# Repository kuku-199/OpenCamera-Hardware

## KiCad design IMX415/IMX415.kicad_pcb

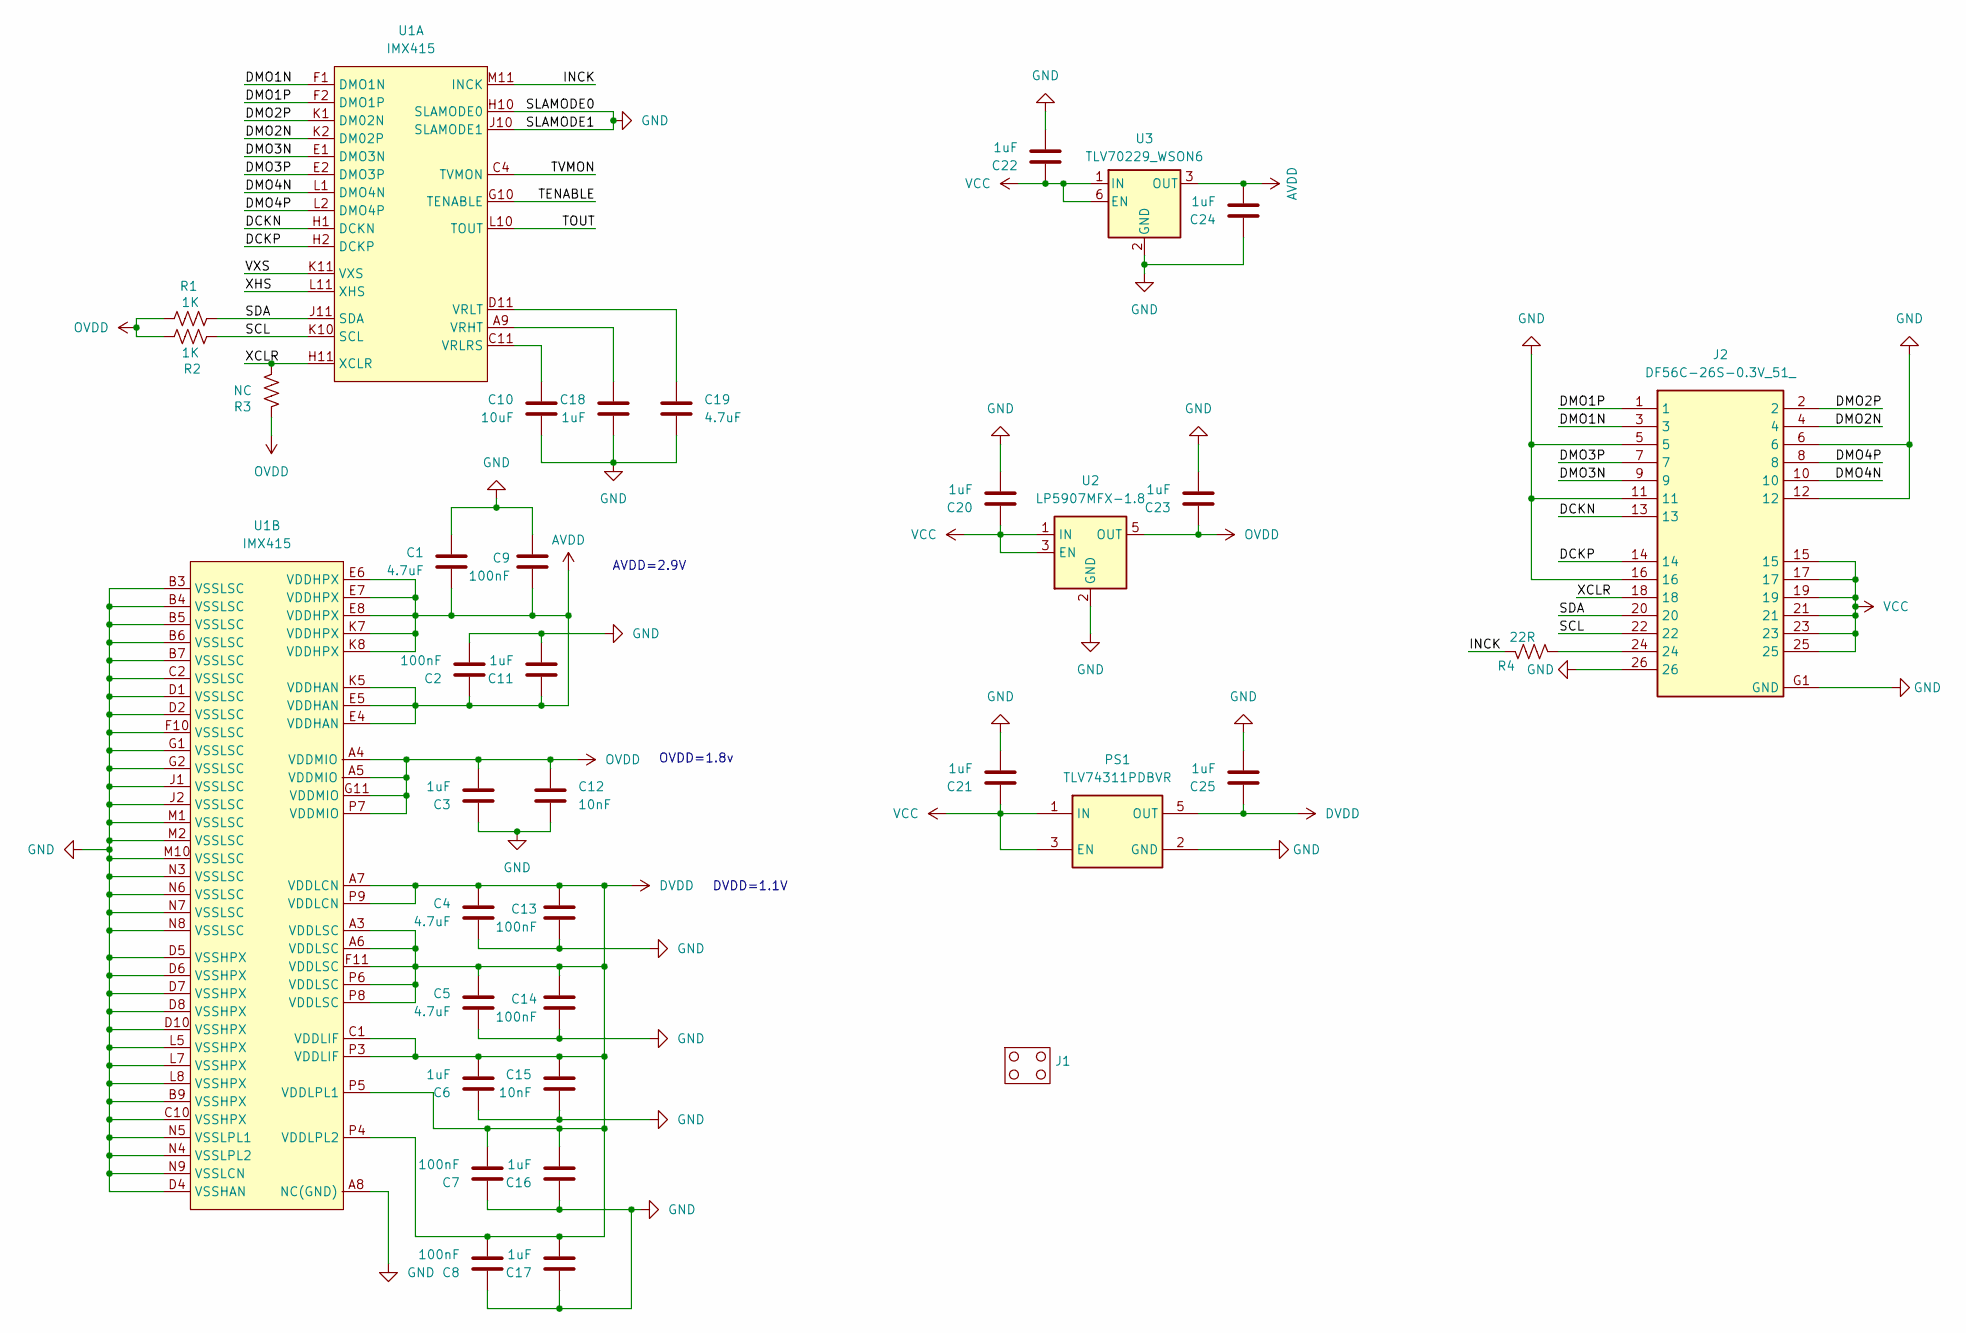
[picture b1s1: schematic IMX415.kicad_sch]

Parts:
C1, C4, C5, C19: 4.7uF; C_0402_1005Metric
C2, C7, C8, C9, C13, C14: 100nF; C_0402_1005Metric
C3, C6, C11, C16, C17, C18, C20, C21, C22, C23, C24, C25: 1uF; C_0402_1005Metric
C10: 10uF; C_0402_1005Metric
C12, C15: 10nF; C_0402_1005Metric
J1: Outline_19X19
J2: DF56C-26S-0.3V_51_; DF56C26S03V51; Manufacturer_Part_Number DF56C-26S-0.3V(51); Mouser Part Number 798-DF56C-26S-0.3V51
PS1: TLV74311PDBVR; SOT95P280X145-5N; Manufacturer_Part_Number TLV74311PDBVR; Mouser Part Number 595-TLV74311PDBVR
R1, R2: 1K; R_0402_1005Metric
R3: NC; R_0402_1005Metric
R4: 22R; R_0402_1005Metric
U1: IMX415
U2: LP5907MFX-1.8; SOT-23-5
U3: TLV70229_WSON6; WSON-6_1.5x1.5mm_P0.5mm

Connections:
/DCKN: J2.13, U1.H1 (DCKN)
/DCKP: J2.14, U1.H2 (DCKP)
/DMO1N: J2.3, U1.F1 (DMO1N)
/DMO1P: J2.1, U1.F2 (DMO1P)
/DMO2N: J2.4, U1.K2 (DM02P)
/DMO2P: J2.2, U1.K1 (DM02N)
/DMO3N: J2.9, U1.E1 (DMO3N)
/DMO3P: J2.7, U1.E2 (DMO3P)
/DMO4N: J2.10, U1.L1 (DMO4N)
/DMO4P: J2.8, U1.L2 (DMO4P)
/INCK: R4.2, U1.M11 (INCK)
/SCL: J2.22, R2.2, U1.K10 (SCL)
/SDA: J2.20, R1.1, U1.J11 (SDA)
/TENABLE: U1.G10 (TENABLE)
/TOUT: U1.L10 (TOUT)
/TVMON: U1.C4 (TVMON)
/VXS: U1.K11 (VXS)
/XCLR: J2.18, R3.1, U1.H11 (XCLR)
/XHS: U1.L11 (XHS)
AVDD: C1.2, C2.1, C9.2, C11.1, C24.2, U1.E4 (VDDHAN), U1.E5 (VDDHAN), U1.E6 (VDDHPX), U1.E7 (VDDHPX), U1.E8 (VDDHPX), U1.K5 (VDDHAN), U1.K7 (VDDHPX), U1.K8 (VDDHPX), U3.3 (OUT)
DVDD: C4.1, C5.1, C6.2, C7.2, C8.2, C13.1, C14.1, C15.2, C16.2, C17.2, C25.1, PS1.5 (OUT), U1.A3 (VDDLSC), U1.A6 (VDDLSC), U1.A7 (VDDLCN), U1.C1 (VDDLIF), U1.F11 (VDDLSC), U1.P3 (VDDLIF), U1.P4 (VDDLPL2), U1.P5 (VDDLPL1), U1.P6 (VDDLSC), U1.P8 (VDDLSC), U1.P9 (VDDLCN)
GND: C1.1, C2.2, C3.1, C4.2, C5.2, C6.1, C7.1, C8.1, C9.1, C10.1, C11.2, C12.1, C13.2, C14.2, C15.1, C16.1, C17.1, C18.1, C19.1, C20.2, C21.2, C22.2, C23.2, C24.1, C25.2, J2.5, J2.6, J2.11, J2.12, J2.16, J2.26, J2.G1 (GND), J2.G2 (GND_2), J2.G3 (GND_3), J2.G4 (GND_4), J2.G5 (GND_5), PS1.2 (GND), U1.A8 (NC(GND)), U1.B3 (VSSLSC), U1.B4 (VSSLSC), U1.B5 (VSSLSC), U1.B6 (VSSLSC), U1.B7 (VSSLSC), U1.B8 (NC(GND)), U1.B9 (VSSHPX), U1.C2 (VSSLSC), U1.C3 (NC(GND)), U1.C5 (NC(GND)), U1.C6 (NC(GND)), U1.C7 (NC(GND)), U1.C8 (NC(GND)), U1.C9 (NC(GND)), U1.C10 (VSSHPX), U1.D1 (VSSLSC), U1.D2 (VSSLSC), U1.D3 (NC(GND)), U1.D4 (VSSHAN), U1.D5 (VSSHPX), U1.D6 (VSSHPX), U1.D7 (VSSHPX), U1.D8 (VSSHPX), U1.D9 (NC(GND)), U1.D10 (VSSHPX), U1.E3 (NC(GND)), U1.E9 (NC(GND)), U1.E10 (NC(GND)), U1.E11 (NC(GND)), U1.F10 (VSSLSC), U1.G1 (VSSLSC), U1.G2 (VSSLSC), U1.H10 (SLAMODE0), U1.J1 (VSSLSC), U1.J2 (VSSLSC), U1.J10 (SLAMODE1), U1.K3 (NC(GND)), U1.K4 (NC(GND)), U1.K6 (NC(GND)), U1.K9 (NC(GND)), U1.L3 (NC(GND)), U1.L4 (NC(GND)), U1.L5 (VSSHPX), U1.L6 (NC(GND)), U1.L7 (VSSHPX), U1.L8 (VSSHPX), U1.L9 (NC(GND)), U1.M1 (VSSLSC), U1.M2 (VSSLSC), U1.M3 (NC(GND)), U1.M4 (NC(GND)), U1.M5 (NC(GND)), U1.M6 (NC(GND)), U1.M7 (NC(GND)), U1.M8 (NC(GND)), U1.M9 (NC(GND)), U1.M10 (VSSLSC), U1.N3 (VSSLSC), U1.N4 (VSSLPL2), U1.N5 (VSSLPL1), U1.N6 (VSSLSC), U1.N7 (VSSLSC), U1.N8 (VSSLSC), U1.N9 (VSSLCN), U2.2 (GND), U3.2 (GND)
unnamed: J2.24, R4.1
unnamed: C18.2, U1.A9 (VRHT)
unnamed: C10.2, U1.C11 (VRLRS)
unnamed: C19.2, U1.D11 (VRLT)
OVDD: C3.2, C12.2, C23.1, R1.2, R2.1, R3.2, U1.A4 (VDDMIO), U1.A5 (VDDMIO), U1.G11 (VDDMIO), U1.P7 (VDDMIO), U2.5 (OUT)
VCC: C20.1, C21.1, C22.1, J2.15, J2.17, J2.19, J2.21, J2.23, J2.25, PS1.1 (IN), PS1.3 (EN), U2.1 (IN), U2.3 (EN), U3.1 (IN), U3.6 (EN)

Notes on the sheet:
DVDD=1.1V
AVDD=2.9V
OVDD=1.8v

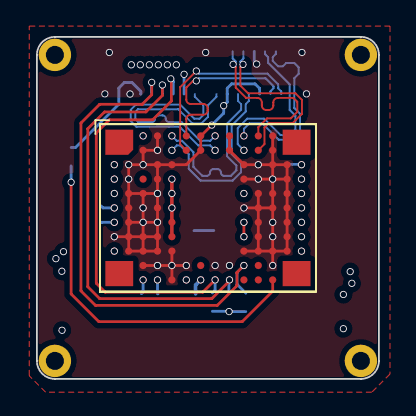
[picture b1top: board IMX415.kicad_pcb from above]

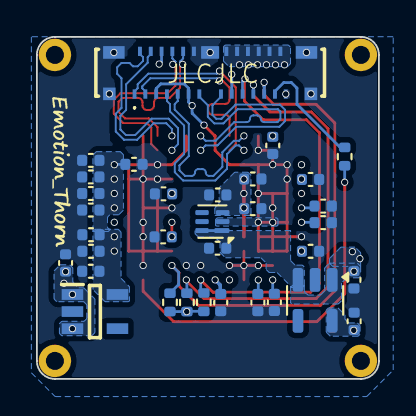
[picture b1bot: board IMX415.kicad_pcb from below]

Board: 4 copper layers, 19.0 x 19.0 mm, 35 parts (33 on the bottom side), 23 nets.

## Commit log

2025-10-20 Add Design files
2025-10-20 Add LICENSE
2025-10-20 Add .gitignore
2025-10-20 Add IMX415
